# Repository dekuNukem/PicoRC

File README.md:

# PicoRC: PicoPSU on Retro Computers!

[Purchase Link](https://www.tindie.com/stores/dekunukem/items/) | [Official Discord](https://discord.gg/HAuuh3pAmB)

----

PicoRC is a line of replacement **Power-supply Units (PSU)** for vintage computers.

## Features

* **Non-destructive** and **reversible**
* Universal voltage with **fused** rails
* **PC Fan header** for added cooling

For more **general-purpose** diagnostics and retrofitting, check out [ATX4VC](https://dekunukem.github.io/ATX4VC/).

## Available For:

### IBM PC Compatible

[Purchase Link](https://www.tindie.com/products/31437) | [Instructions](ibmpc.md)

### IBM Portable Personal Computer 5155

[Purchase Link](https://www.tindie.com/products/31437) | [Instructions](ibm5155.md)

### Apple II / II Plus / IIe

[Purchase Link](https://www.tindie.com/products/29185/) | [Instructions](appleii.md)

### Apple IIGS

[Purchase Link](https://www.tindie.com/products/30055/) | [Instructions](apple_iigs.md)

### Macintosh 128K / 512K / Plus

[Purchase Link](https://www.tindie.com/products/28754/) | [Instructions](og_mac.md)

### Macintosh SE & SE/30

[Purchase Link](https://www.tindie.com/products/29184/) | [Instructions](mac_se_se30.md)

### BBC Micro

[Purchase Link](https://www.tindie.com/products/31079/) | [Instructions](bbc_micro.md)

### BBC Master

[Purchase Link](https://www.tindie.com/products/31079/) | [Instructions](bbc_master.md)

### ACT Sirius 1 / Victor 9000

[Purchase Link](https://www.tindie.com/products/41802/) | [Instructions](sirius1.md)

### Apricot PC / PC XI / PC286

[Purchase Link](https://www.tindie.com/products/31080/) | [Instructions](apricot_pc.md)

### Osborne 1

[Purchase Link](https://www.tindie.com/products/30087/) | [Instructions](osborne1.md)

## Get in Touch

Join our official [Discord Chatroom](https://discord.gg/T9uuFudg7j) for updates.

Questions or comments? Ask in Discord, or raise a [Github issue](https://github.com/dekuNukem/ATX4VC/issues), or email `dekunukem` `gmail.com`!

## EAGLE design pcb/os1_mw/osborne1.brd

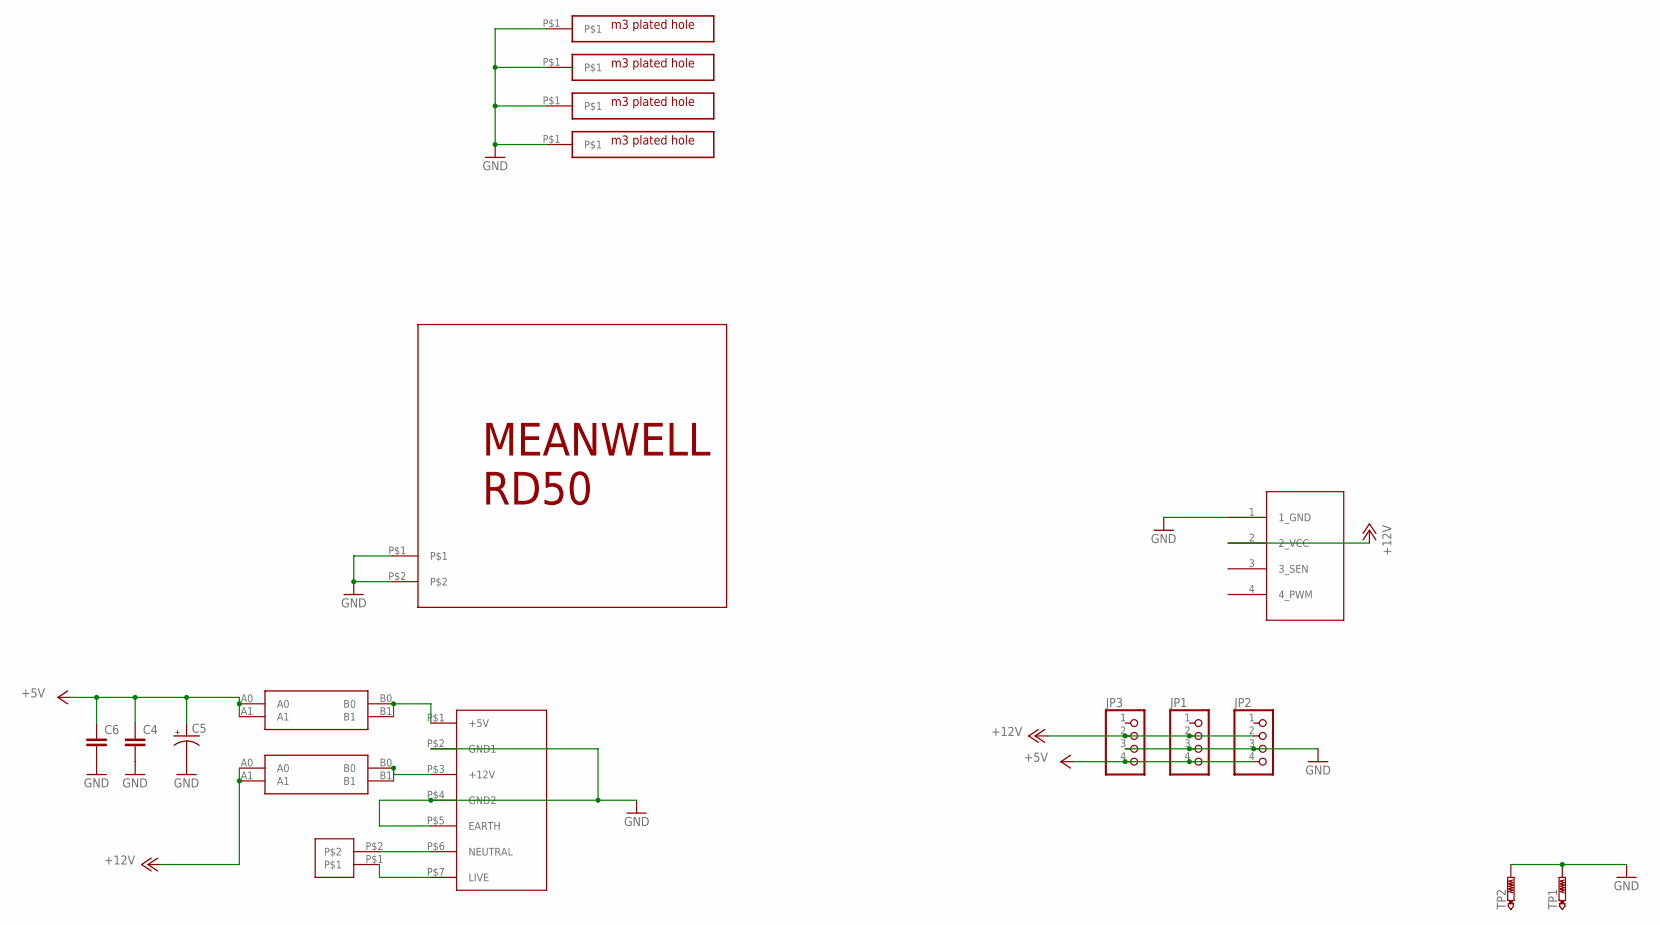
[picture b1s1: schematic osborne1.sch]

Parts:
C4, C6: C5/2.5; C5B2.5
C5: CPOL-USE3.5-8; E3,5-8
JP1, JP2, JP3: PINHD-1X4/90; 1X04/90
JP4: 4PIN_FAN; 1X04
TP1, TP2: PTR1PAD1-17; P1-17
U$1: MEANWELL_RD50
U$2: 396_2P_LIVE
U$3: TERM_RD50_MAINS; TERMINAL9500_MAINS
U$4, U$5, U$6, U$8: M3_HOLE_PLATED
U$7, U$9: CAR_FUSE_HOLDER3IN1; FUSE_HOLDER_3IN1

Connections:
+5V: C4.1, C5.+, C6.1, JP1.4, JP2.4, JP3.4, U$9.A0, U$9.A1
+12V: JP1.2, JP2.2, JP3.2, JP4.2 (2_VCC), U$7.A0, U$7.A1
GND: C4.2, C5.-, C6.2, JP1.3, JP2.3, JP3.3, JP4.1 (1_GND), TP1.TP, TP2.TP, U$1.P$1, U$1.P$2, U$3.P$2 (GND1), U$3.P$4 (GND2), U$3.P$5 (EARTH), U$4.P$1, U$5.P$1, U$6.P$1, U$8.P$1
unnamed: U$3.P$3 (+12V), U$7.B0, U$7.B1
unnamed: U$3.P$1 (+5V), U$9.B0, U$9.B1
unnamed: U$2.P$2, U$3.P$6 (NEUTRAL)
unnamed: U$2.P$1, U$3.P$7 (LIVE)

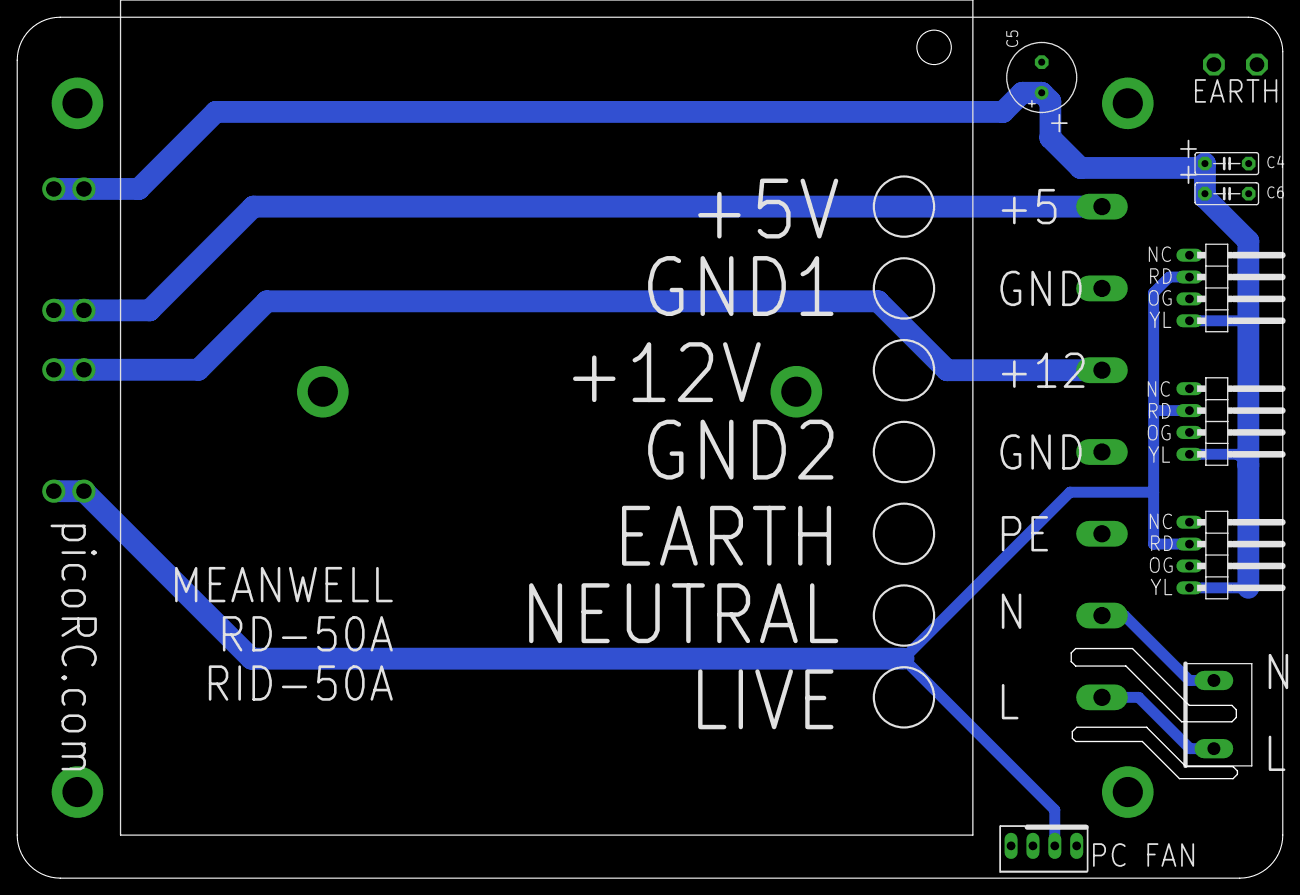
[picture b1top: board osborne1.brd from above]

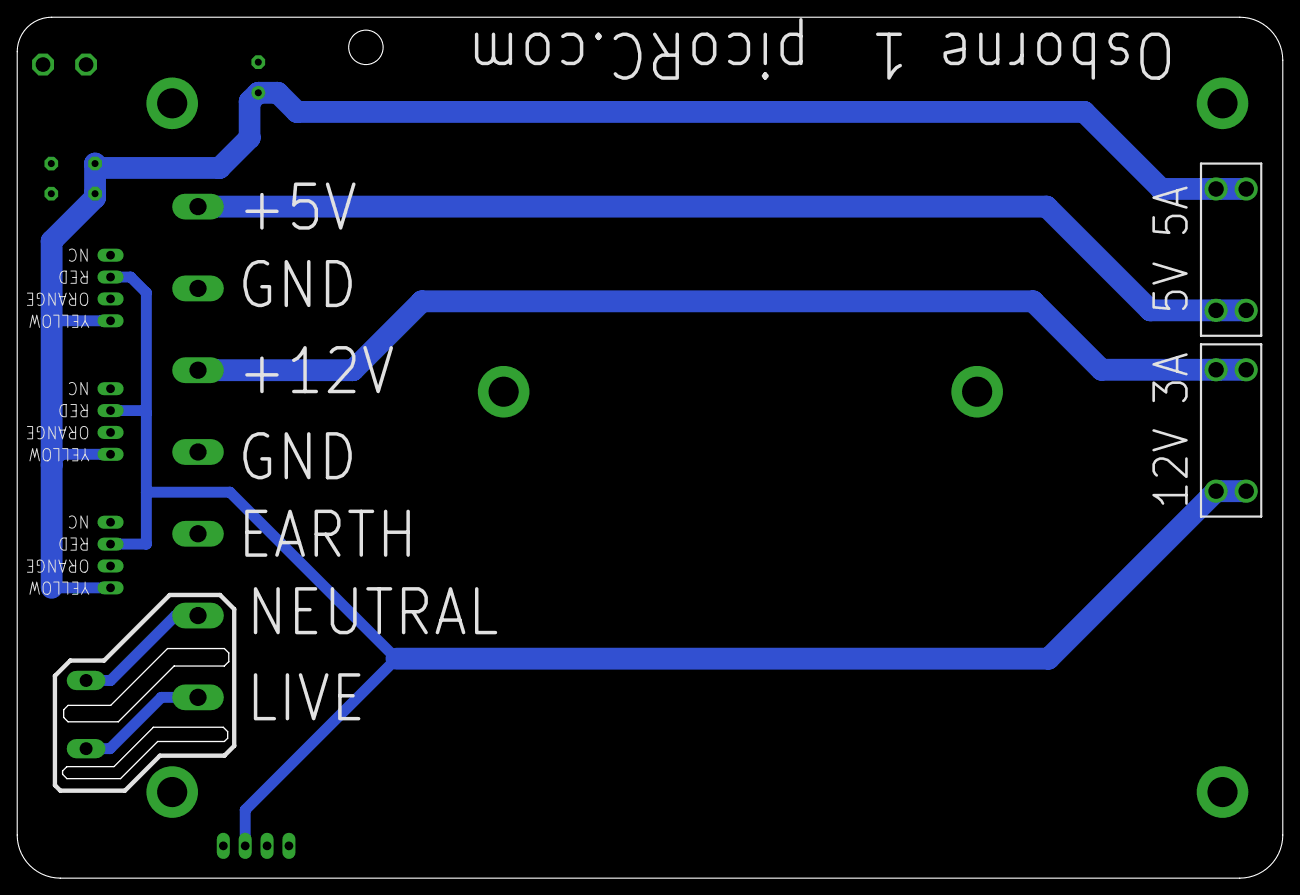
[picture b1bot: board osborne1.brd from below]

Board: 2 copper layers, 147.0 x 100.0 mm, 18 parts (2 on the bottom side), 7 nets.

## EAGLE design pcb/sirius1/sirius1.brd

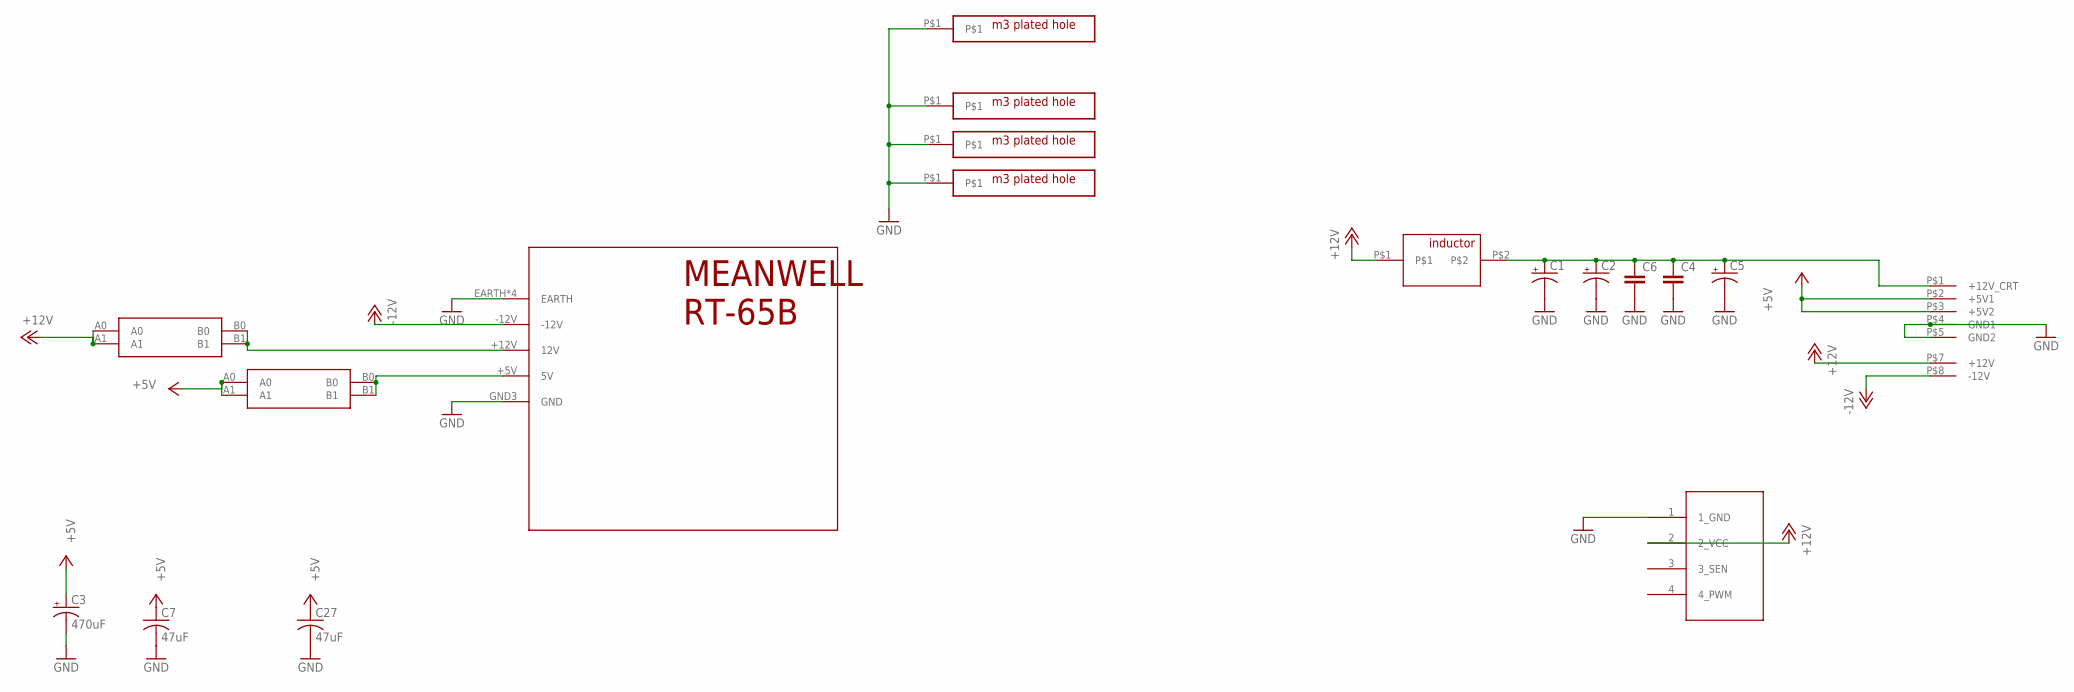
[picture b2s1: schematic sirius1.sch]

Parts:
C1, C2, C5: CPOL-USE3.5-8; E3,5-8
C3: 470uF; SMC_D
C4, C6: C5/2.5; C5B2.5
C7, C27: 47uF; C1210
JP4: 4PIN_FAN; 1X04
U$1, U$2, U$4, U$5: M3_HOLE_PLATEDM3; M3_HOLE_PLATED
U$6: 396_SIRIUS1
U$7: MEANWELL_RT65
U$8, U$9: CAR_FUSE_HOLDER3IN1; FUSE_HOLDER_3IN1
U$10: INDUCTOR_PTH_8MM

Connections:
+5V: C3.+, C7.1, C27.1, U$6.P$2 (+5V1), U$6.P$3 (+5V2), U$8.A0, U$8.A1
+12V: JP4.2 (2_VCC), U$6.P$7 (+12V), U$9.A0, U$9.A1, U$10.P$1
-12V: U$6.P$8 (-12V), U$7.-12V
GND: C1.-, C2.-, C3.-, C4.2, C5.-, C6.2, C7.2, C27.2, JP4.1 (1_GND), U$1.P$1, U$2.P$1, U$4.P$1, U$5.P$1, U$6.P$4 (GND1), U$6.P$5 (GND2), U$7.EARTH, U$7.GND (EARTH), U$7.GND1 (EARTH), U$7.GND2 (EARTH), U$7.GND3 (GND)
unnamed: C1.+, C2.+, C4.1, C5.+, C6.1, U$6.P$1 (+12V_CRT), U$10.P$2
unnamed: U$7.+5V (5V), U$8.B0, U$8.B1
unnamed: U$7.+12V (12V), U$9.B0, U$9.B1

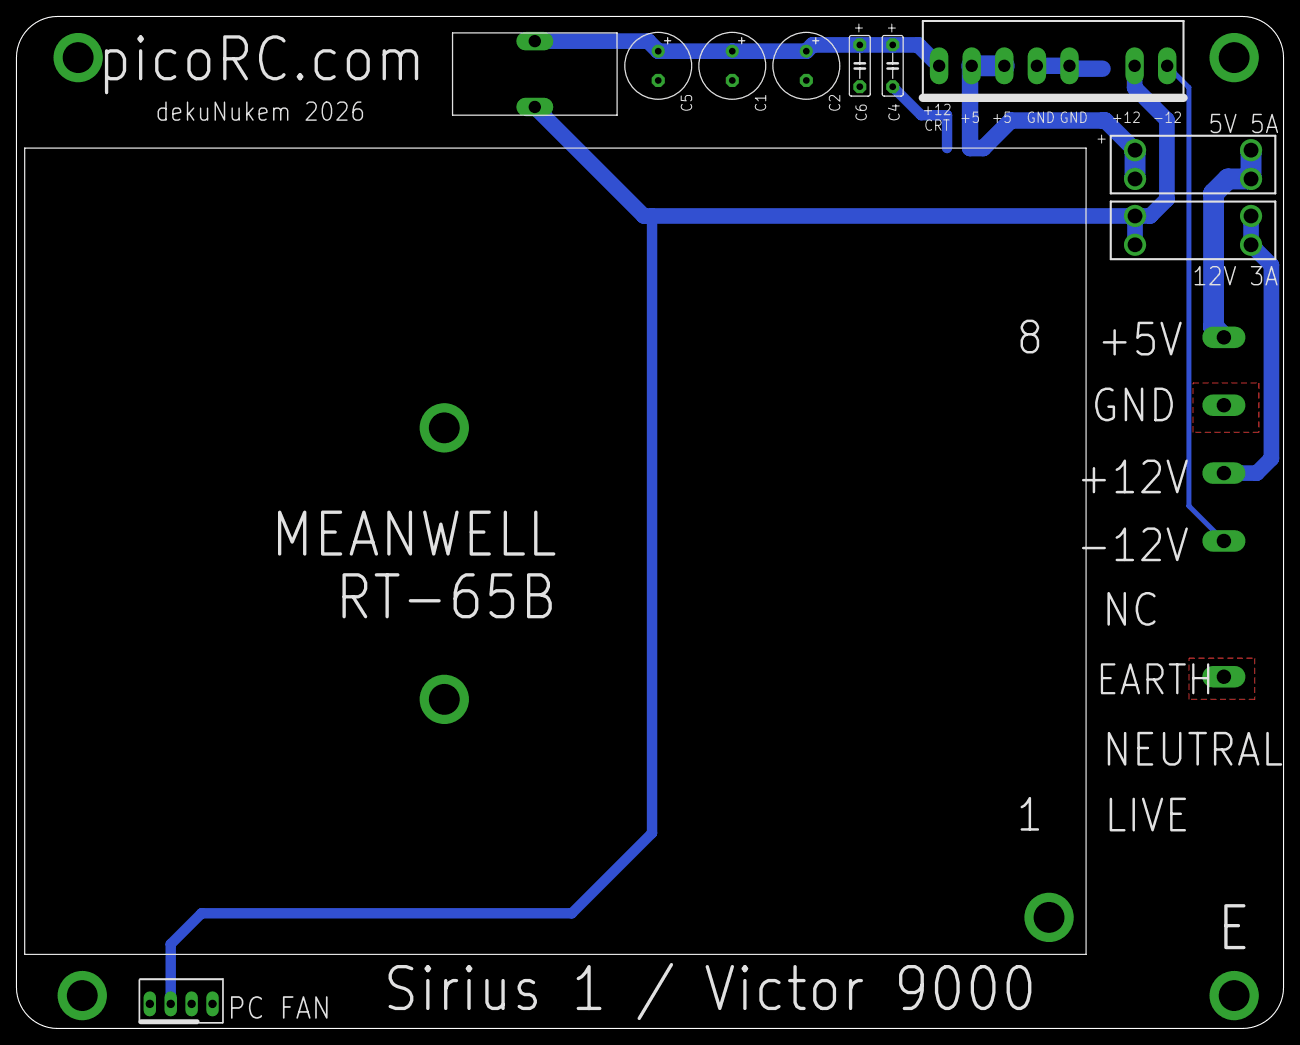
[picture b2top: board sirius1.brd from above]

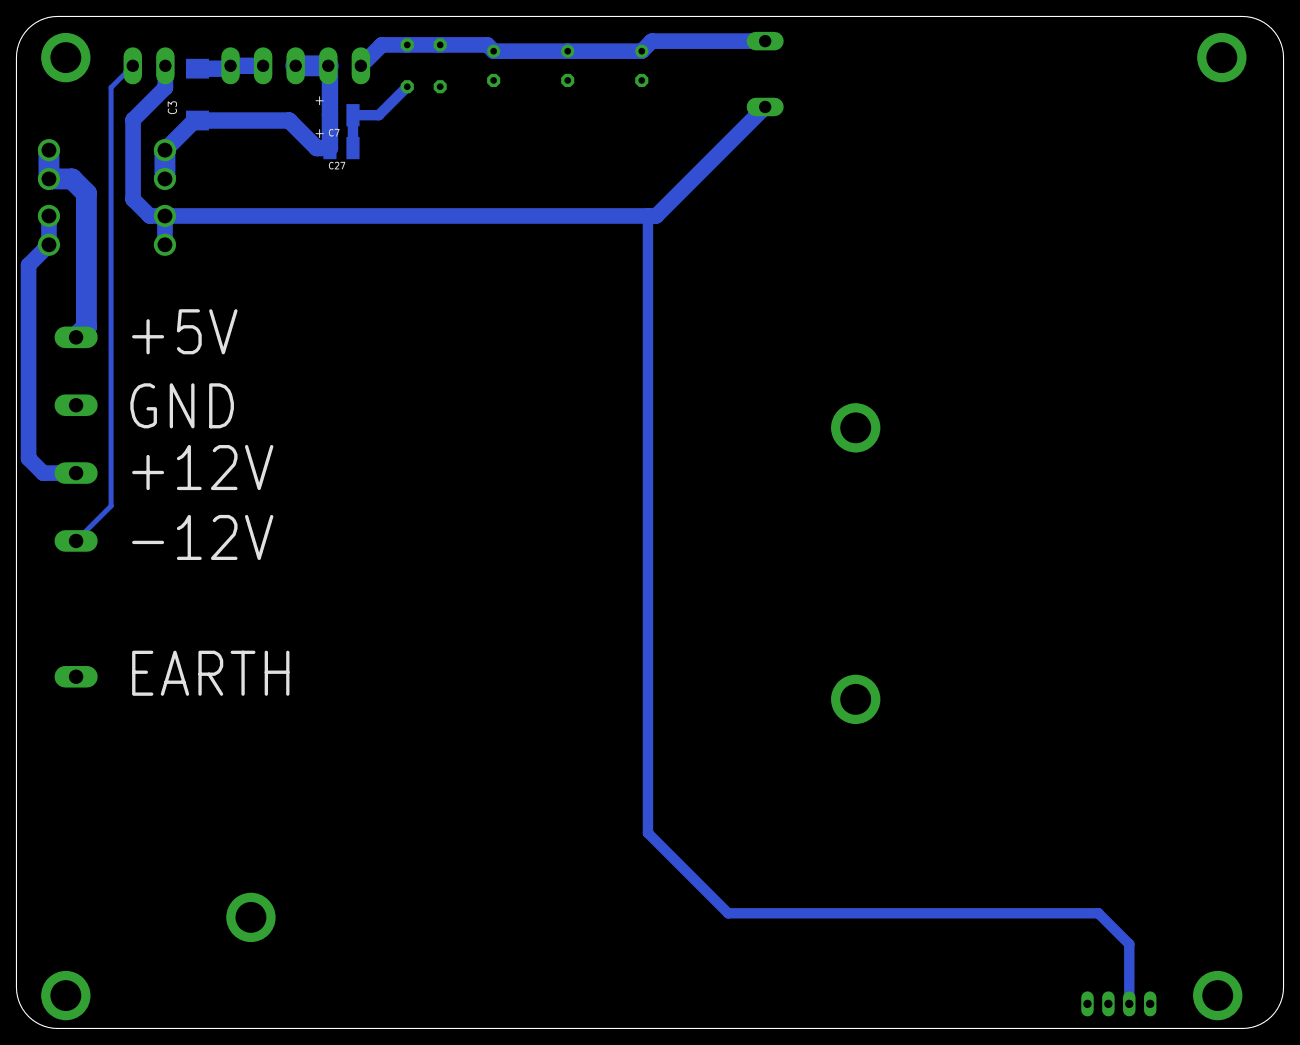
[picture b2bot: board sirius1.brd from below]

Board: 2 copper layers, 154.0 x 123.0 mm, 18 parts (7 on the bottom side), 7 nets.

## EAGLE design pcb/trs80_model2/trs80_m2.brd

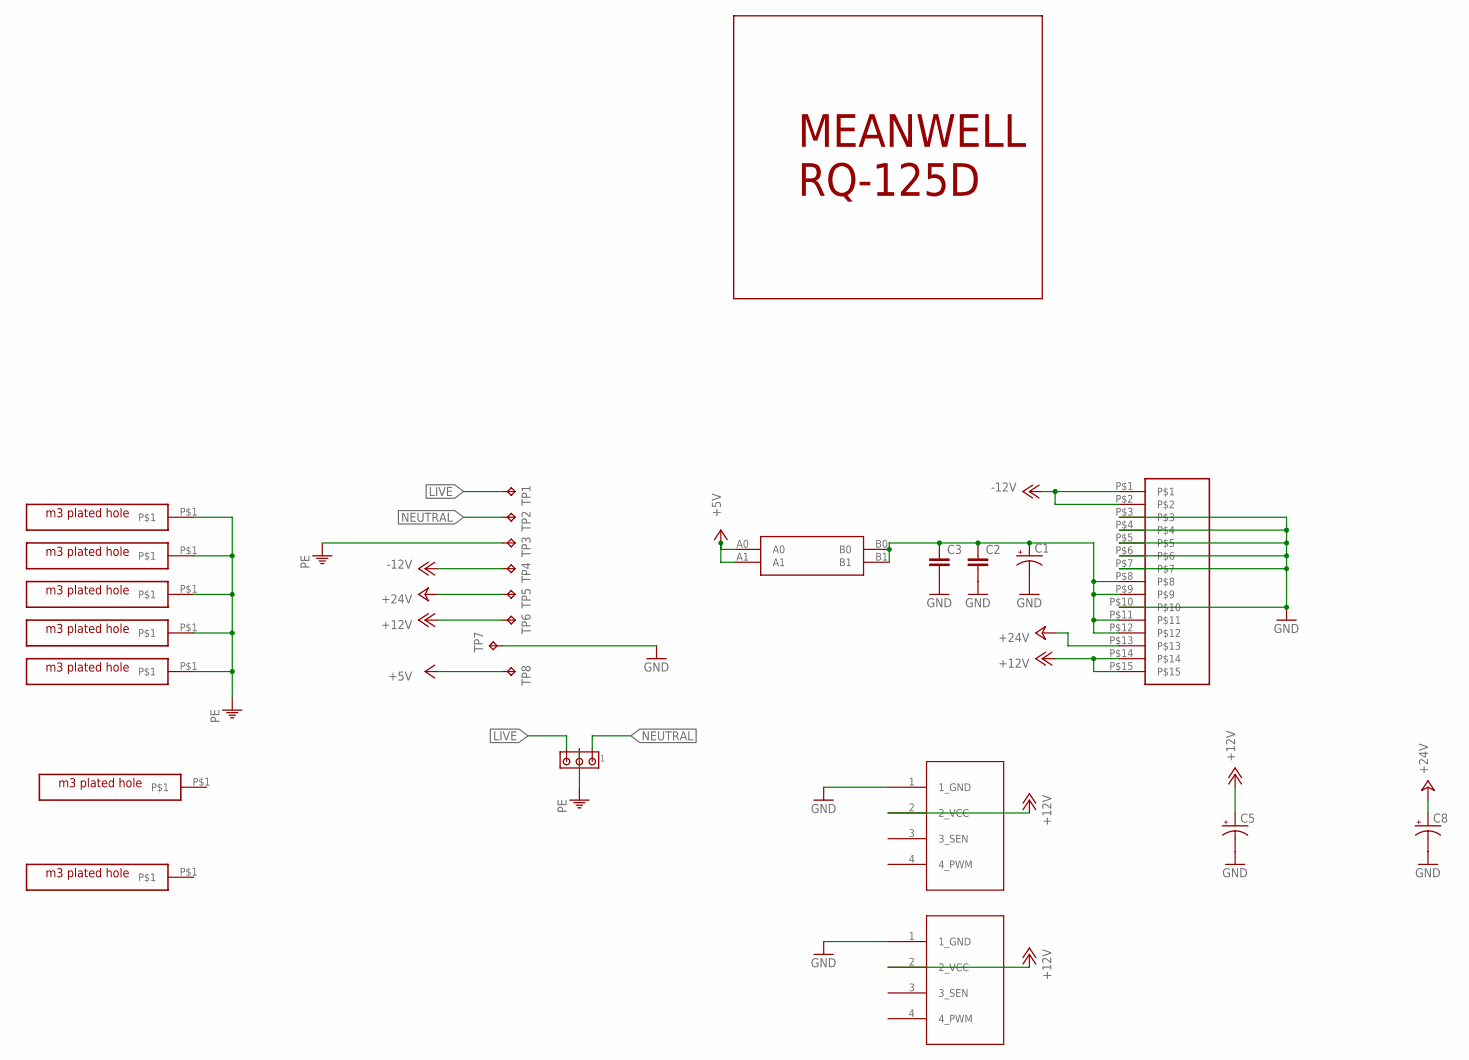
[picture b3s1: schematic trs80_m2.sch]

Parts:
C1, C5, C8: CPOL-USE3.5-8; E3,5-8
C2, C3: C5/2.5; C5B2.5
J1: 350760-4
JP1, JP4: 4PIN_FAN; 1X04
TP1, TP2, TP3, TP4, TP5, TP6, TP7, TP8: TPPAD1-20Y; P1-20Y
U$2: MEANWELL_RQ_125D; MEANWELL_RQ125D
U$3: TE_3X5; TRS80M2_3X5
U$4, U$5, U$6, U$7, U$8, U$10, U$11: M3_HOLE_PLATED
U$9: CAR_FUSE_HOLDER3IN1; FUSE_HOLDER_3IN1

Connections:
+5V: TP8.TP, U$9.A0, U$9.A1
+12V: C5.+, JP1.2 (2_VCC), JP4.2 (2_VCC), TP6.TP, U$3.P$14, U$3.P$15
+24V: C8.+, TP5.TP, U$3.P$13
-12V: TP4.TP, U$3.P$1, U$3.P$2
GND: C1.-, C2.2, C3.2, C5.-, C8.-, JP1.1 (1_GND), JP4.1 (1_GND), TP7.TP, U$3.P$3, U$3.P$4, U$3.P$5, U$3.P$6, U$3.P$7, U$3.P$10
LIVE: J1.3, TP1.TP
unnamed: C1.+, C2.1, C3.1, U$3.P$8, U$3.P$9, U$3.P$11, U$3.P$12, U$9.B0, U$9.B1
NEUTRAL: J1.1, TP2.TP
PE: J1.2, TP3.TP, U$4.P$1, U$5.P$1, U$6.P$1, U$7.P$1, U$8.P$1

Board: 2 copper layers, 26 parts (0 on the bottom side), 9 nets, no tracks yet.

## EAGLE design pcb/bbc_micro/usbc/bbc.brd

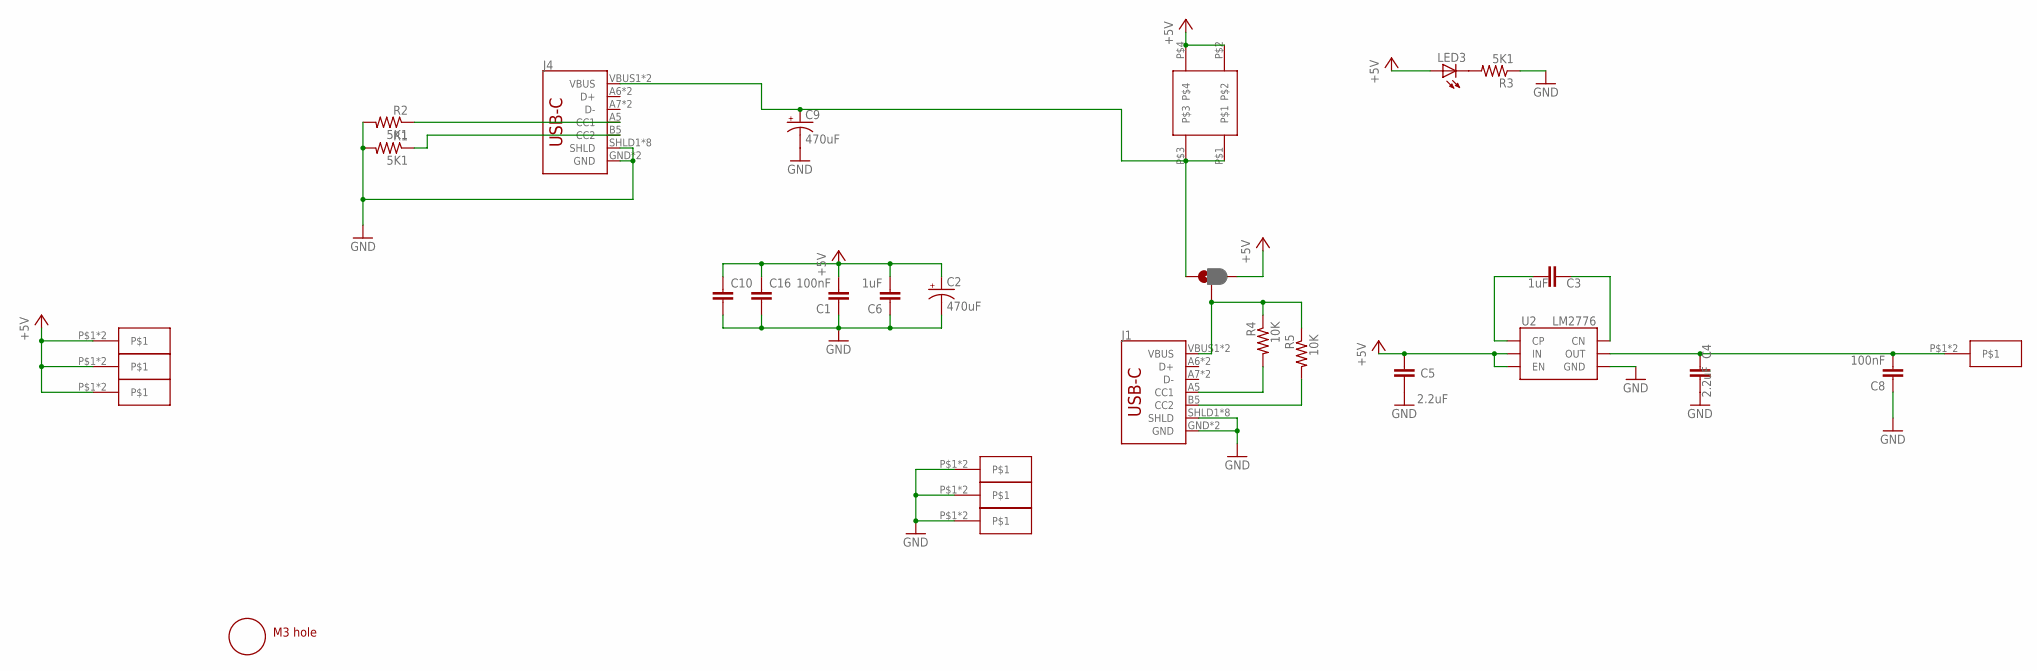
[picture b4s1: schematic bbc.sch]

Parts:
C1, C8: 100nF; 0805@1
C2, C9: 470uF; SMC_D
C3, C6: 1uF; 0805@1
C4, C5: 2.2uF; 0805@1
C10, C16: C5/2.5; C5B2.5
J1, J4: USB_C16PIN; USB-C-16P
JP1: JUMPER-SMT_3_1-NC_PASTE_NO-SILK; SMT-JUMPER_3_1-NC_PASTE_NO-SILK
LED3: LEDCHIP-LED0805; CHIP-LED0805
R1, R2, R3: 5K1; 0805
R4, R5: 10K; 0805
U2: LM2776; SOT-23-6
U$3: ROCK_SW; ROCK_SWITCH
U$4: M3_MOUNTING_HOLE; M3_MOUNTING_HOLE_PACK
U$5, U$6, U$7, U$8, U$9, U$10, U$11: BLADE28; 2.8BLADE

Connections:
+5V: C1.2, C2.+, C5.1, C6.2, C10.1, C16.1, JP1.3, LED3.A, U2.3 (IN), U2.4 (EN), U$3.P$2, U$3.P$4, U$6.P$1, U$6.P$2, U$7.P$1, U$7.P$2, U$8.P$1, U$8.P$2
GND: C1.1, C2.-, C4.2, C5.2, C6.1, C8.1, C9.-, C10.2, C16.2, J1.GND, J1.GND2 (GND), J1.SHLD1 (SHLD), J1.SHLD2 (SHLD), J1.SHLD3 (SHLD), J1.SHLD4 (SHLD), J1.SHLD5 (SHLD), J1.SHLD6 (SHLD), J1.SHLD7 (SHLD), J1.SHLD8 (SHLD), J4.GND, J4.GND2 (GND), J4.SHLD1 (SHLD), J4.SHLD2 (SHLD), J4.SHLD3 (SHLD), J4.SHLD4 (SHLD), J4.SHLD5 (SHLD), J4.SHLD6 (SHLD), J4.SHLD7 (SHLD), J4.SHLD8 (SHLD), R1.2, R2.2, R3.1, U2.2 (GND), U$9.P$1, U$9.P$2, U$10.P$1, U$10.P$2, U$11.P$1, U$11.P$2
unnamed: C9.+, J4.VBUS1 (VBUS), J4.VBUS2 (VBUS), JP1.1, U$3.P$1, U$3.P$3
unnamed: C3.2, U2.5 (CP)
unnamed: C3.1, U2.6 (CN)
unnamed: C4.1, C8.2, U2.1 (OUT), U$5.P$1, U$5.P$2
unnamed: J1.VBUS1 (VBUS), J1.VBUS2 (VBUS), JP1.2, R4.1, R5.1
unnamed: J4.A5 (CC1), R2.1
unnamed: LED3.C, R3.2
unnamed: J1.B5 (CC2), R5.2
unnamed: J1.A5 (CC1), R4.2
unnamed: J4.B5 (CC2), R1.1

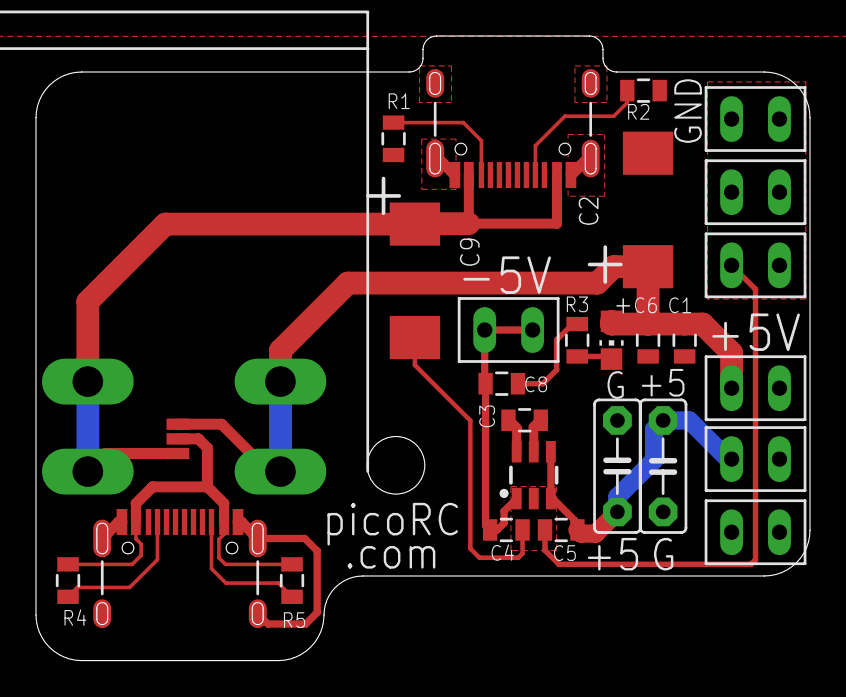
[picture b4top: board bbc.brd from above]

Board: 2 copper layers, 43.0 x 34.7 mm, 29 parts (0 on the bottom side), 12 nets.

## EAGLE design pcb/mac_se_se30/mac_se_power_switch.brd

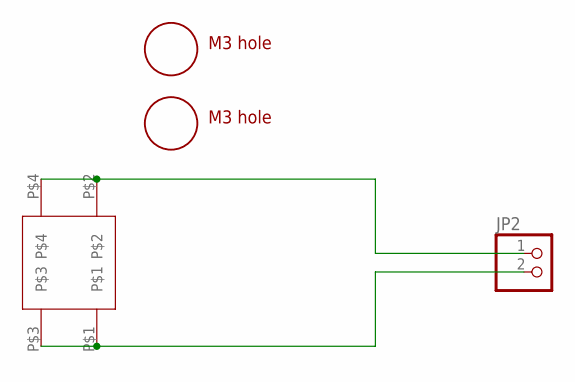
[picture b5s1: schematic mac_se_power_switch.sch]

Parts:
JP2: PINHD-1X2/90; 1X02/90
U$1: ROCK_SW; ROCK_SWITCH
U$2, U$3: M3_MOUNTING_HOLE; M3_MOUNTING_HOLE_PACK

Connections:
unnamed: JP2.2, U$1.P$1, U$1.P$3
unnamed: JP2.1, U$1.P$2, U$1.P$4

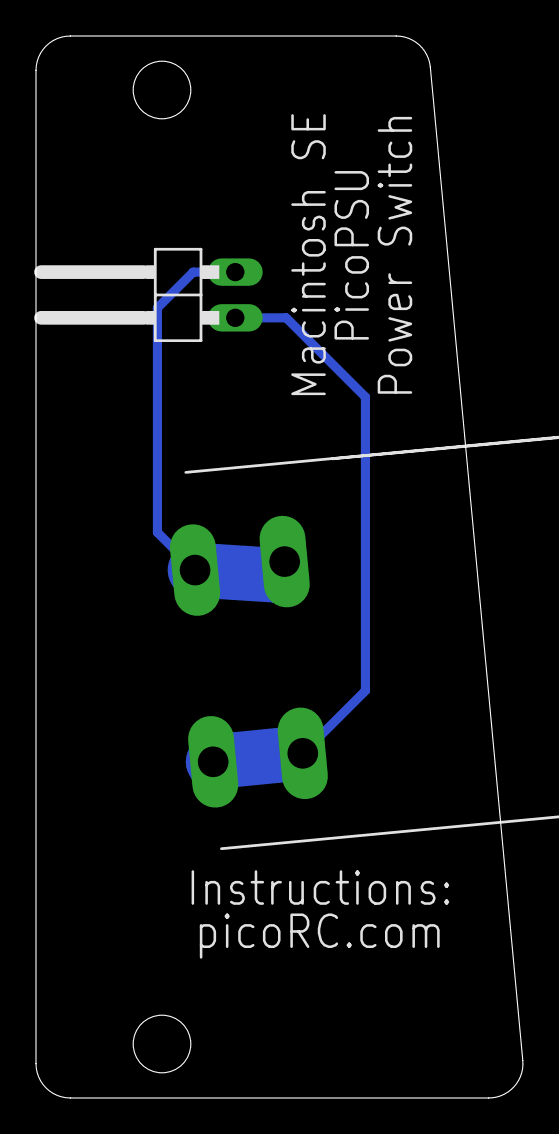
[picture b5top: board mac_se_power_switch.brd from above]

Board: 2 copper layers, 27.1 x 59.0 mm, 4 parts (0 on the bottom side), 2 nets.

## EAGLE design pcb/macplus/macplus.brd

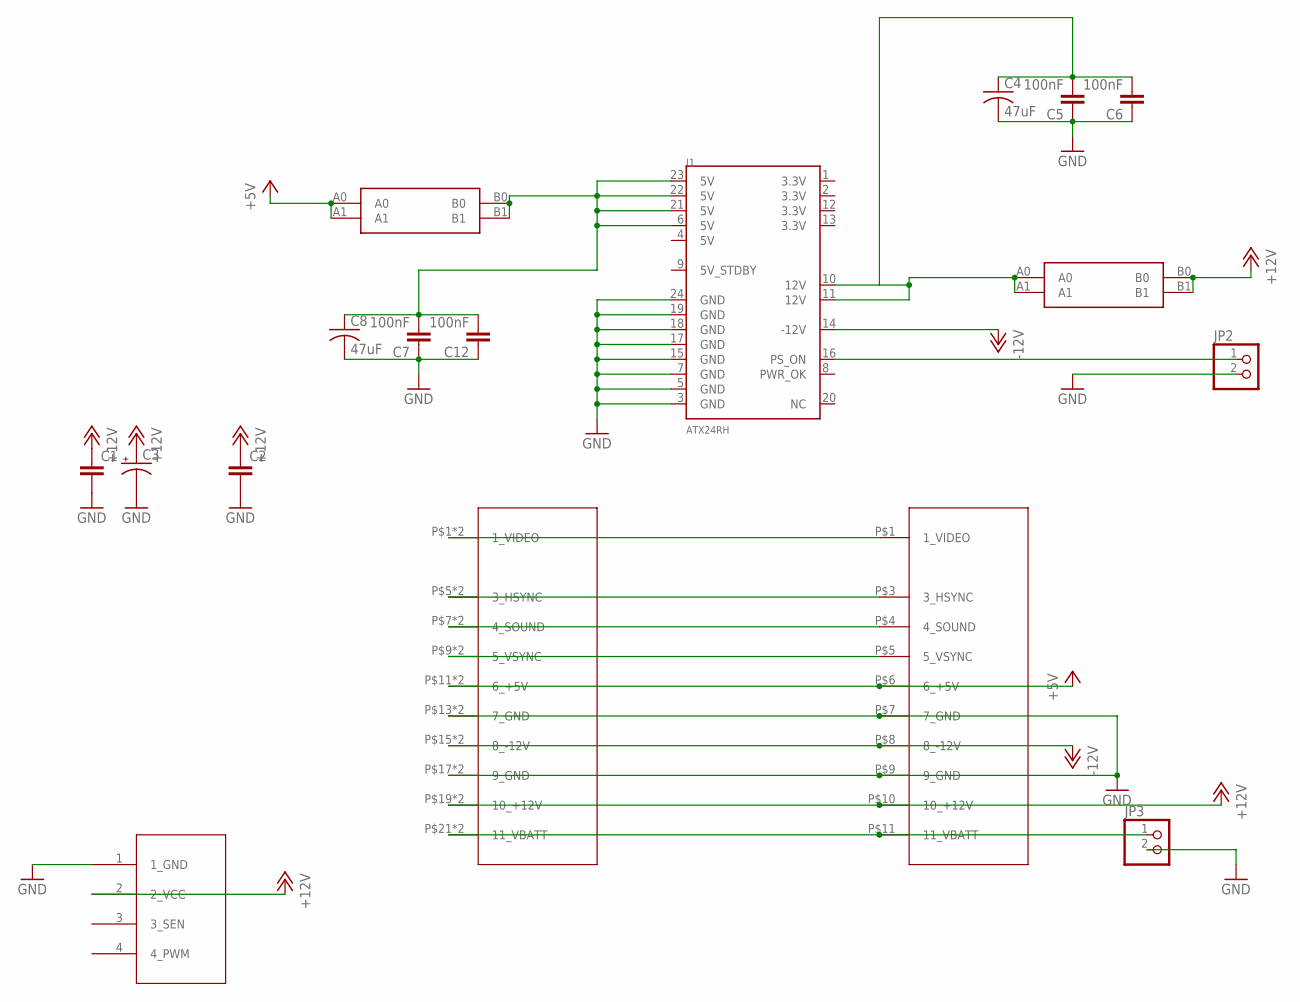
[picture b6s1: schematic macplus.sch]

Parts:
C1, C2: C5/2.5; C5B2.5
C3: CPOL-USE3.5-8; E3,5-8
C4, C8: 47uF; C1210
C5, C6, C7, C12: 100nF; 0805@1
J1: ATX24RH; ATX24_STRAIGHT
JP1: 4PIN_FAN; 1X04
JP2, JP3: PINHD-1X2; 1X02
U$1: MACPLUS; 396_10P
U$2, U$8: CAR_FUSE_HOLDER3IN1; FUSE_HOLDER_3IN1
U$3: 3.96_FEM; 3.96_FEMALE_GAP

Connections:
+5V: U$1.P$6 (6_+5V), U$3.P$11 (6_+5V), U$3.P$12 (6_+5V), U$8.A0, U$8.A1
+12V: C1.1, C2.1, C3.+, JP1.2 (2_VCC), U$1.P$10 (10_+12V), U$2.B0, U$2.B1, U$3.P$19 (10_+12V), U$3.P$20 (10_+12V)
-12V: J1.14 (-12V), U$1.P$8 (8_-12V), U$3.P$15 (8_-12V), U$3.P$16 (8_-12V)
GND: C1.2, C2.2, C3.-, C4.2, C5.1, C6.1, C7.1, C8.2, C12.1, J1.3 (GND), J1.5 (GND), J1.7 (GND), J1.15 (GND), J1.17 (GND), J1.18 (GND), J1.19 (GND), J1.24 (GND), JP1.1 (1_GND), JP2.2, JP3.2, U$1.P$7 (7_GND), U$1.P$9 (9_GND), U$3.P$13 (7_GND), U$3.P$14 (7_GND), U$3.P$17 (9_GND), U$3.P$18 (9_GND)
unnamed: U$1.P$1 (1_VIDEO), U$3.P$1 (1_VIDEO), U$3.P$2 (1_VIDEO)
unnamed: U$1.P$3 (3_HSYNC), U$3.P$5 (3_HSYNC), U$3.P$6 (3_HSYNC)
unnamed: U$1.P$4 (4_SOUND), U$3.P$7 (4_SOUND), U$3.P$8 (4_SOUND)
unnamed: U$1.P$5 (5_VSYNC), U$3.P$9 (5_VSYNC), U$3.P$10 (5_VSYNC)
unnamed: J1.16 (PS_ON), JP2.1
unnamed: C7.2, C8.1, C12.2, J1.6 (5V), J1.21 (5V), J1.22 (5V), J1.23 (5V), U$8.B0, U$8.B1
unnamed: C4.1, C5.2, C6.2, J1.10 (12V), J1.11 (12V), U$2.A0, U$2.A1
unnamed: JP3.1, U$1.P$11 (11_VBATT), U$3.P$21 (11_VBATT), U$3.P$22 (11_VBATT)

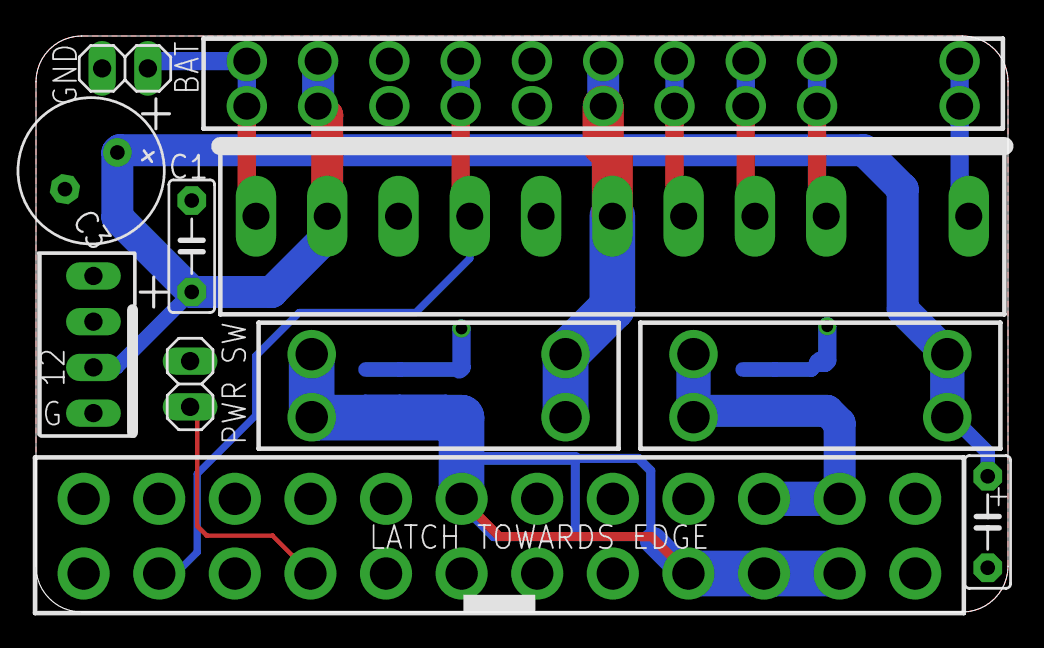
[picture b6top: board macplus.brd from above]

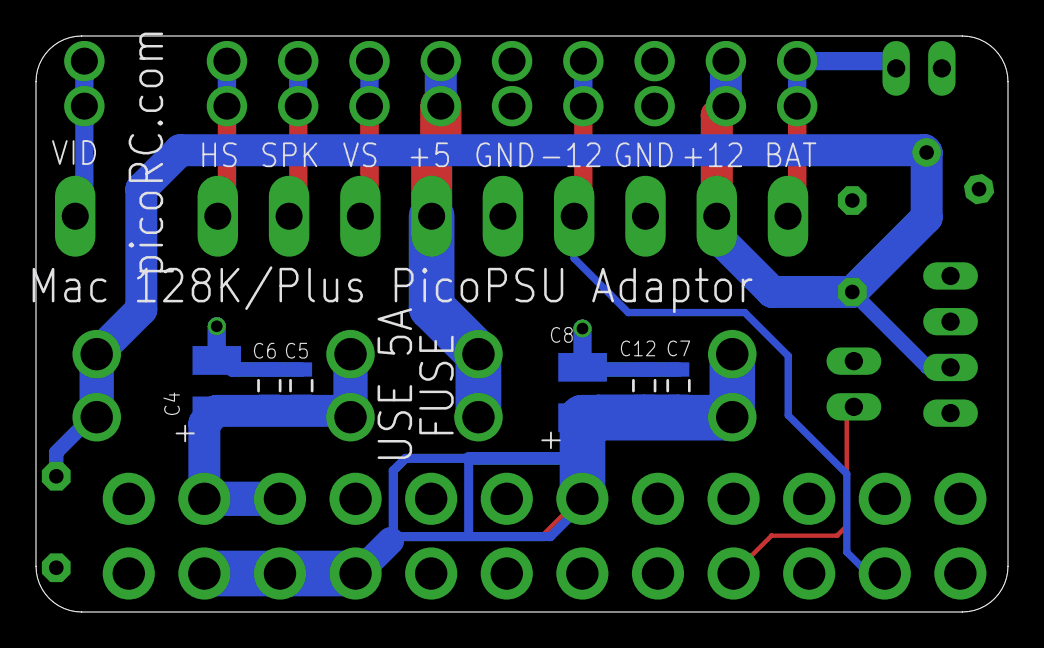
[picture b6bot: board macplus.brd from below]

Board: 2 copper layers, 54.0 x 32.0 mm, 17 parts (6 on the bottom side), 12 nets.

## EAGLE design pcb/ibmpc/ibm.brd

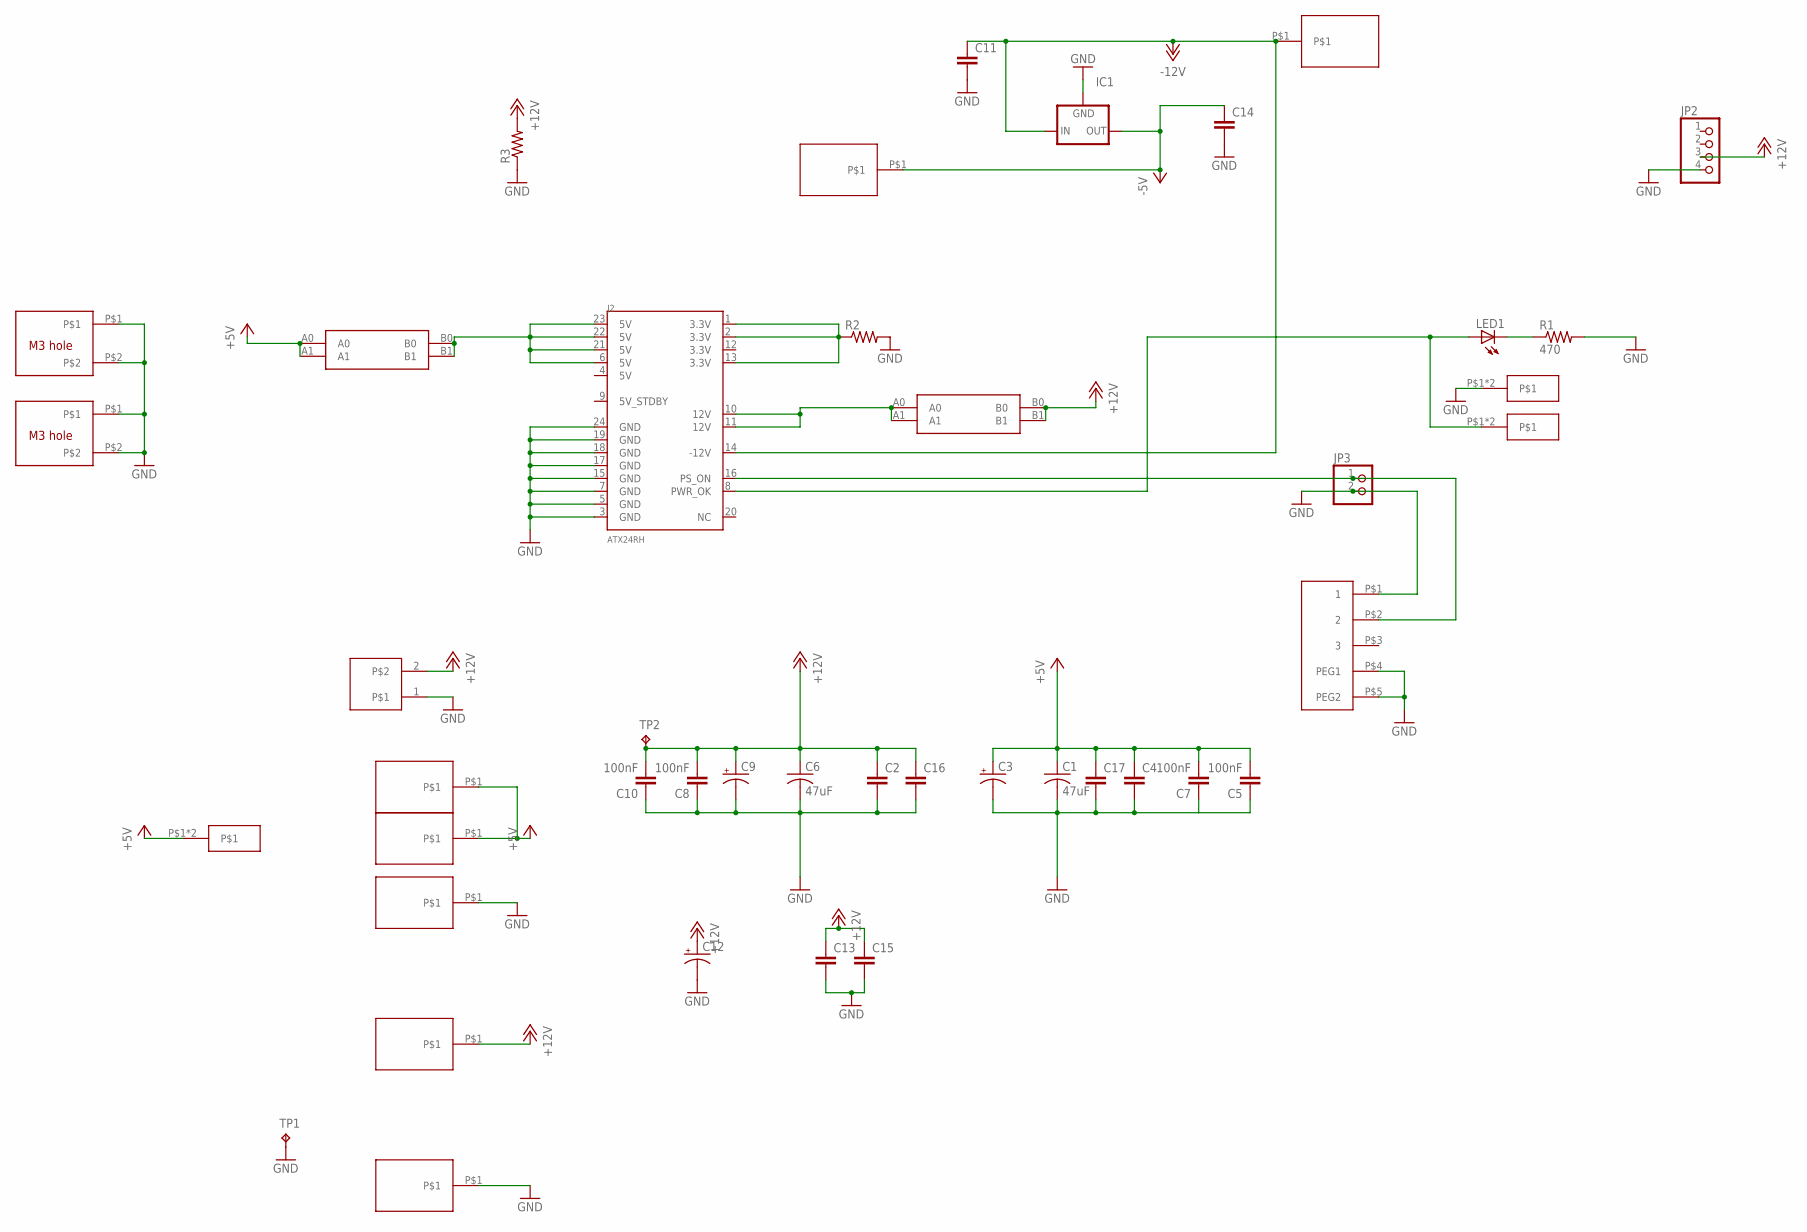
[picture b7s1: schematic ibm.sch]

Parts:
C1, C6: 47uF; C1210
C2, C4, C11, C13, C14, C15, C16, C17: C5/2.5; C5B2.5
C3, C9, C12: CPOL-USE3.5-8; E3,5-8
C5, C7, C8, C10: 100nF; 0805@1
IC1: 79XXS
J2: ATX24RH; ATX24_RIGHT_ANGLE
JP2: PINHD-1X4/90; 1X04/90
JP3: PINHD-1X2/90; 1X02/90
LED1: LED5MM
R1: 470; 0207/10
R2, R3: R-US_0411/15; 0411/15
TP1, TP2: TPPAD1-13; P1-13
U$1, U$7, U$9, U$10, U$13, U$15, U$16: ISA; ISAPAD
U$2, U$8: CAR_FUSE_HOLDER3IN1; FUSE_HOLDER_3IN1
U$3, U$11, U$14: 28FLAG; 2.8FLAG
U$4: ROCKSW
U$5, U$6: M3_MOUNTING_HOLE; M3_MOUNTING_HOLE_PACK
U$12: CRT2P

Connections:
+5V: C1.1, C3.+, C4.1, C5.2, C7.2, C17.1, U$1.P$1, U$8.A0, U$8.A1, U$11.P$1, U$11.P$2, U$16.P$1
+12V: C2.1, C6.1, C8.2, C9.+, C10.2, C12.+, C13.1, C15.1, C16.1, JP2.3, R3.2, TP2.TP, U$2.B0, U$2.B1, U$12.2, U$13.P$1
-5V: C14.1, IC1.OUT, U$7.P$1
-12V: C11.1, IC1.IN, J2.14 (-12V), U$10.P$1
GND: C1.2, C2.2, C3.-, C4.2, C5.1, C6.2, C7.1, C8.1, C9.-, C10.1, C11.2, C12.-, C13.2, C14.2, C15.2, C16.2, C17.2, IC1.GND, J2.3 (GND), J2.5 (GND), J2.7 (GND), J2.15 (GND), J2.17 (GND), J2.18 (GND), J2.19 (GND), J2.24 (GND), JP2.4, JP3.2, R1.2, R2.2, R3.1, TP1.TP, U$4.P$1 (1), U$4.P$4 (PEG1), U$4.P$5 (PEG2), U$5.P$1, U$5.P$2, U$6.P$1, U$6.P$2, U$9.P$1, U$12.1, U$14.P$1, U$14.P$2, U$15.P$1
unnamed: J2.1 (3.3V), J2.2 (3.3V), J2.13 (3.3V), R2.1
unnamed: J2.16 (PS_ON), JP3.1, U$4.P$2 (2)
unnamed: J2.8 (PWR_OK), LED1.A, U$3.P$1, U$3.P$2
unnamed: J2.6 (5V), J2.21 (5V), J2.22 (5V), J2.23 (5V), U$8.B0, U$8.B1
unnamed: J2.10 (12V), J2.11 (12V), U$2.A0, U$2.A1
unnamed: LED1.K (C), R1.1

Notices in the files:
parts and their libraries:
SparkFun-Connectors: Licensing: Creative Commons ShareAlike 4.0 International - https://creativecommons.org/licenses/by-sa/4.0
